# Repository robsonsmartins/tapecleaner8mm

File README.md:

# 8mm Tape Cleaner
The 8mm Tape Cleaner is a machine for cleaning and removing mildew from 8mm tapes from Sony camcorders.

Project site: [8mm Tape Cleaner Project](https://www.robsonmartins.com/content/eletr/projects/tapeclean8/)

[![CC BY-NC-SA 4.0][cc-by-nc-sa-shield]][cc-by-nc-sa]

This work is licensed under a
[Creative Commons Attribution-NonCommercial-ShareAlike 4.0 International License][cc-by-nc-sa].

[![CC BY-NC-SA 4.0][cc-by-nc-sa-image]][cc-by-nc-sa]

[cc-by-nc-sa]: http://creativecommons.org/licenses/by-nc-sa/4.0/
[cc-by-nc-sa-image]: https://licensebuttons.net/l/by-nc-sa/4.0/88x31.png
[cc-by-nc-sa-shield]: https://img.shields.io/badge/License-CC%20BY--NC--SA%204.0-lightgrey.svg

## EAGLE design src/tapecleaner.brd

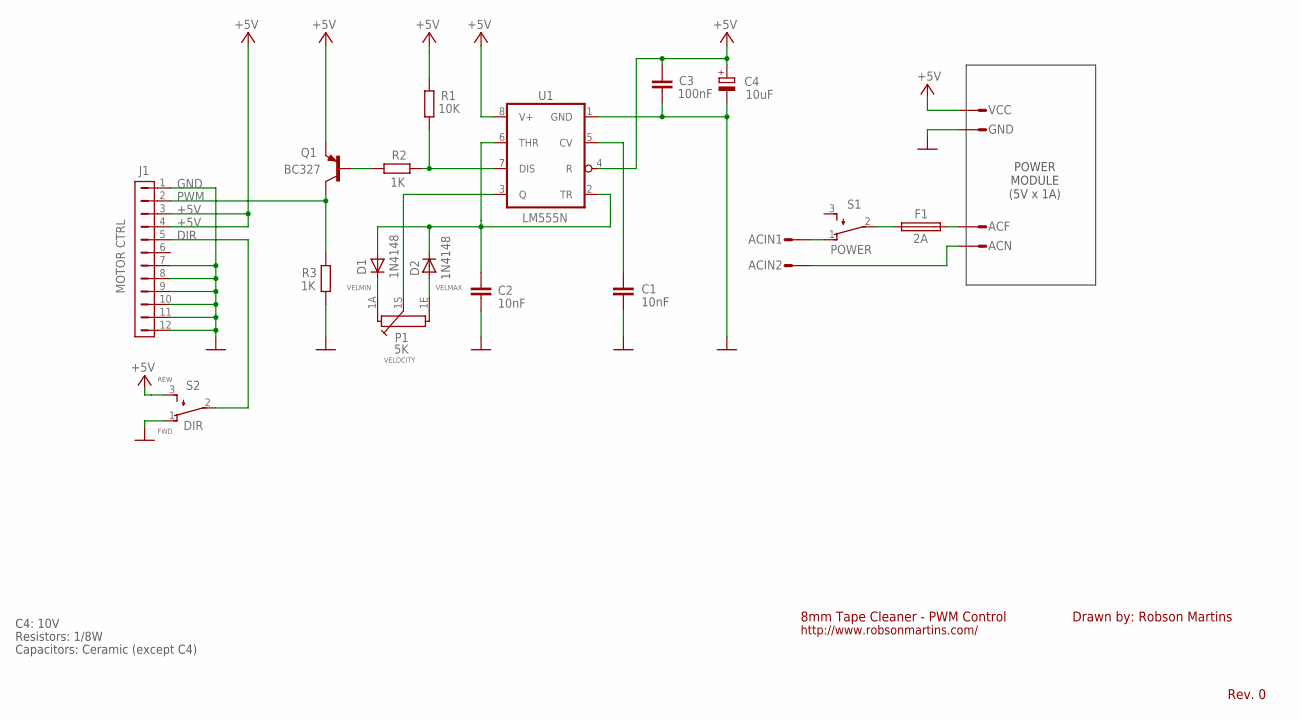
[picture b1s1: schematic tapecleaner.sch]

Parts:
ACF: ST2,8
ACIN1, ACIN2: ST2,8
ACN: ST2,8
C1, C2: 10nF; C050-025X075
C3: 100nF; C050-025X075
C4: 10uF; E2,5-6E
D1, D2: 1N4148; DO35-7
F1: 2A; SHK20L
GND: ST2,8
J1: MOTOR CTRL; FH21-12S-1DSA
P1: 5K; PC16S
Q1: BC327; TO92
R1: 10K; 0204/7
R2, R3: 1K; 0204/7
S1: POWER; TL3XWO
S2: DIR; TL3XWO
U1: LM555N; DIL08
VCC: ST2,8

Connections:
555CV: C1.1, U1.5 (CV)
555DIS: R1.2, R2.2, U1.7 (DIS)
555TR: C2.1, D1.A, D2.C, U1.2 (TR), U1.6 (THR)
+5V: C3.1, C4.+, J1.3, J1.4, Q1.1 (E), R1.1, S2.3 (S), U1.4 (R), U1.8 (V+), VCC.1
ACIN1: ACIN1.1, S1.1 (O)
ACIN1_PWR: F1.1A (1), S1.2
ACIN2: ACIN2.1, ACN.1
DIR: J1.5, S2.2
GND: C1.2, C2.2, C3.2, C4.-, GND.1, J1.1, J1.7, J1.8, J1.9, J1.10, J1.11, J1.12, R3.2, S2.1 (O), U1.1 (GND)
unnamed: ACF.1, F1.2A (2)
PWM: J1.2, Q1.3 (C), R3.1
Q2B: Q1.2 (B), R2.1
VEL: P1.1S, U1.3 (Q)
VELMAX: D2.A, P1.1E
VELMIN: D1.C, P1.1A

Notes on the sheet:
Rev. 0
Drawn by: Robson Martins
8mm Tape Cleaner - PWM Control
http://www.robsonmartins.com/
C4: 10V
Resistors: 1/8W
Capacitors: Ceramic (except C4)
POWER MODULE (5V x 1A)
VELOCITY
REW
FWD

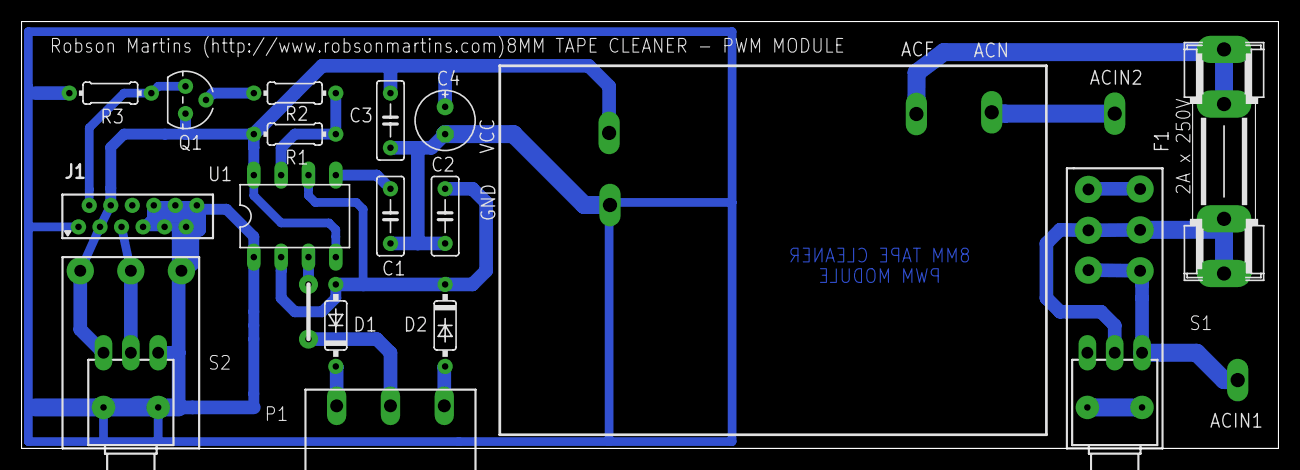
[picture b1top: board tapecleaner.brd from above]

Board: 2 copper layers, 116.8 x 39.7 mm, 22 parts (0 on the bottom side), 15 nets.

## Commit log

2022-01-29 Initial version (1.0)
